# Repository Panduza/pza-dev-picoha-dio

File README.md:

# Pico Host Adapter Dio

This project aims to turn the Raspberry Pi Pico into an USB Host Adapter to control each Digital Input/Output.

## Install firmware on your Pico

[SEE Firmware Documentation](firmware/README.md)

## USB Commands

Commands on USB are based on:

- SLIP [Serial Line Internet Protocol](https://fr.wikipedia.org/wiki/Serial_Line_Internet_Protocol)
- Protobuf [From Google](https://protobuf.dev/)

The USB class used is CDC, it means that you can open it as a serial port.

You must then prepare a Protobuf message with the given specification:

```
firmware\src\api_dio.proto
```

Finally encode the message with SLIP then send it on the serial port.

## Commands examples

For example to set the pin 2 to OUTPUT (by default pins are in INPUT)

```protobuf
message PicohaDioRequest {
    RequestType type = 1;  => SET_PIN_DIRECTION OUTPUT
    uint32 pin_num = 2;    2
    PinValue value = 3;    => OUTPUT
}
```

The board should respond with

```protobuf
message PicohaDioAnswer {
    AnswerType type = 1;                => SUCCESS
    optional PinValue value = 2;
    optional string error_message = 3;
}
```

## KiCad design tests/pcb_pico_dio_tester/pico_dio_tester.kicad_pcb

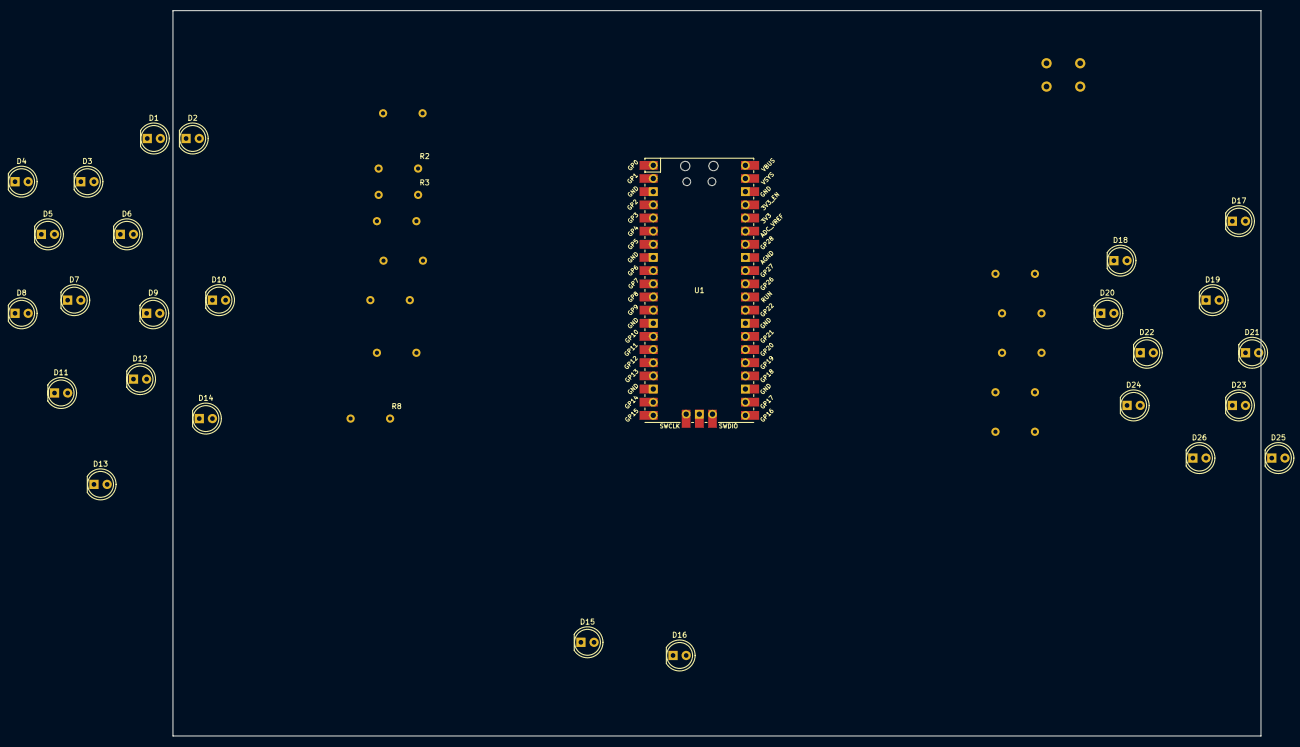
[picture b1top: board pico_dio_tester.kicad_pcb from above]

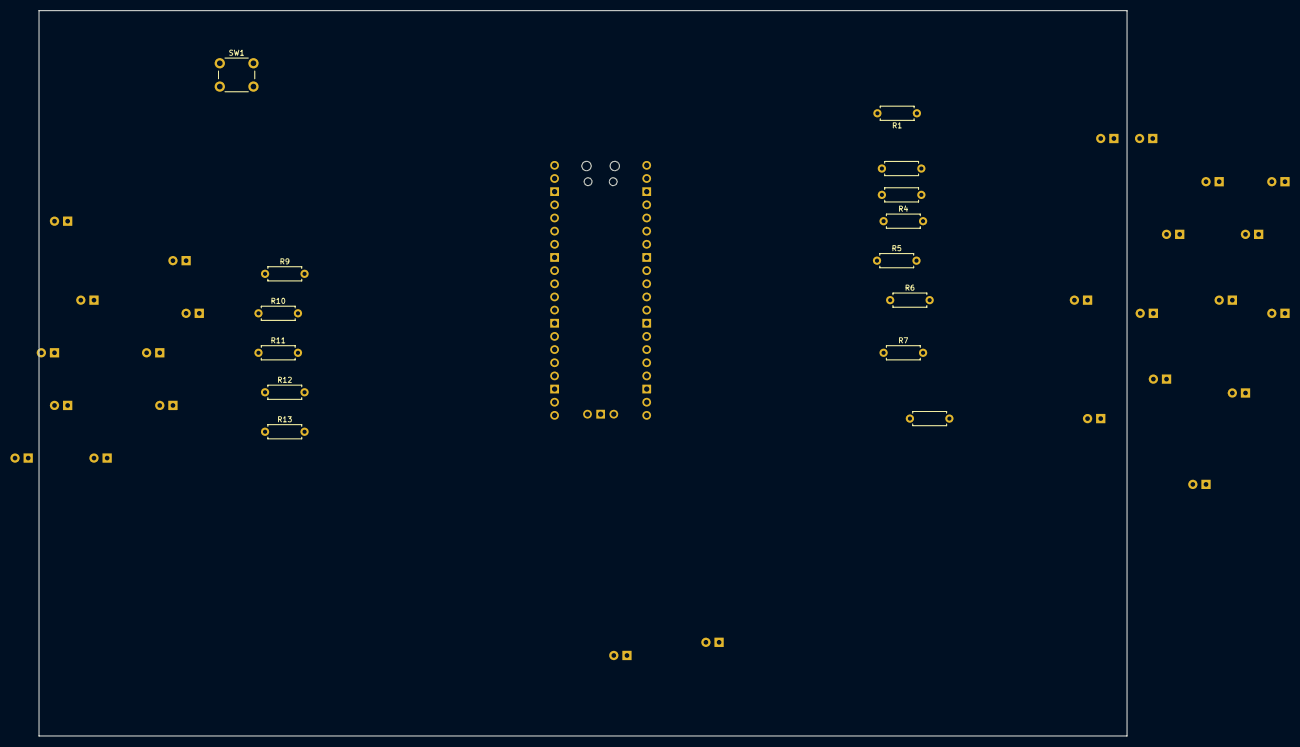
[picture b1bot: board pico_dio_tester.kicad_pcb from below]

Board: 2 copper layers, 210.0 x 140.0 mm, 41 parts (14 on the bottom side), 41 nets, no tracks yet.

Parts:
D1, D2, D3, D4, D5, D6, D7, D8, D9, D10, D11, D12, D13, D14, D15, D16, D17, D18, D19, D20, D21, D22, D23, D24, D25, D26: LD271; LED_D5.0mm_IRGrey
R1, R2, R3, R4, R5, R6, R7, R8, R9, R10, R11, R12, R13: 100R; R_Axial_DIN0207_L6.3mm_D2.5mm_P7.62mm_Horizontal
SW1: SW_Push; SW_PUSH_6mm_H5mm
U1: Pico; RPi_Pico_SMD_TH

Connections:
GND: SW1.2, U1.3 (GND), U1.8 (GND), U1.13 (GND), U1.18 (GND), U1.23 (GND), U1.28 (GND), U1.38 (GND)
GPIO_A_0: R1.2, U1.1 (GPIO0)
GPIO_A_1: R2.2, U1.4 (GPIO2)
GPIO_A_2: R3.2, U1.6 (GPIO4)
GPIO_A_3: R4.2, U1.9 (GPIO6)
GPIO_A_4: R5.2, U1.11 (GPIO8)
GPIO_A_5: R6.2, U1.14 (GPIO10)
GPIO_A_6: R7.2, U1.16 (GPIO12)
GPIO_A_7: R8.2, U1.19 (GPIO14)
GPIO_A_8: R9.2, U1.34 (GPIO28_ADC2)
GPIO_A_9: R10.2, U1.31 (GPIO26_ADC0)
GPIO_A_10: R11.2, U1.27 (GPIO21)
GPIO_A_11: R12.2, U1.25 (GPIO19)
GPIO_A_12: R13.2, U1.22 (GPIO17)
GPIO_B_0: D1.1 (K), D2.2 (A), U1.2 (GPIO1)
GPIO_B_1: D3.1 (K), D4.2 (A), U1.5 (GPIO3)
GPIO_B_2: D5.1 (K), D6.2 (A), U1.7 (GPIO5)
GPIO_B_3: D7.1 (K), D8.2 (A), U1.10 (GPIO7)
GPIO_B_4: D9.1 (K), D10.2 (A), U1.12 (GPIO9)
GPIO_B_5: D11.1 (K), D12.2 (A), U1.15 (GPIO11)
GPIO_B_6: D13.1 (K), D14.2 (A), U1.17 (GPIO13)
GPIO_B_7: D15.1 (K), D16.2 (A), U1.20 (GPIO15)
GPIO_B_8: D17.1 (K), D18.2 (A), U1.32 (GPIO27_ADC1)
GPIO_B_9: D19.1 (K), D20.2 (A), U1.29 (GPIO22)
GPIO_B_10: D21.1 (K), D22.2 (A), U1.26 (GPIO20)
GPIO_B_11: D23.1 (K), D24.2 (A), U1.24 (GPIO18)
GPIO_B_12: D25.1 (K), D26.2 (A), U1.21 (GPIO16)
unnamed: D1.2 (A), D2.1 (K), R1.1
unnamed: D3.2 (A), D4.1 (K), R2.1
unnamed: D5.2 (A), D6.1 (K), R3.1
unnamed: D7.2 (A), D8.1 (K), R4.1
unnamed: D9.2 (A), D10.1 (K), R5.1
unnamed: D11.2 (A), D12.1 (K), R6.1
unnamed: D13.2 (A), D14.1 (K), R7.1
unnamed: D15.2 (A), D16.1 (K), R8.1
unnamed: D17.2 (A), D18.1 (K), R9.1
unnamed: D19.2 (A), D20.1 (K), R10.1
unnamed: D21.2 (A), D22.1 (K), R11.1
unnamed: D23.2 (A), D24.1 (K), R12.1
unnamed: D25.2 (A), D26.1 (K), R13.1
RUN: SW1.1, U1.30 (RUN)

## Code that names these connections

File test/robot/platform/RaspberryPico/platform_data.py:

"""
This file describe Raspberry Pico test bench setup.
"""

import logging, os
from configparser import ConfigParser


_init_file = os.path.join(os.path.dirname(__file__), "config_file.ini")
PORT_COM_DUT: str = ""
if os.path.exists(_init_file):
    logging.info(f"Load config from :{_init_file}")
    _config = ConfigParser()
    _config.read(_init_file)
    PORT_COM_DUT = (
        _config.get("General", "PortCOM")
        if _config.has_option("General", "PortCOM")
        else ""
    )
else:
    logging.info(f"we didn't found: {_init_file}.")

BUILTIN_LED = 25
GPIO_UART = [0, 1]
GPIO_USABLE = [
    2,
    3,
    4,
    5,
    6,
    7,
    8,
    9,
    10,
    11,
    12,
    13,
    14,
    15,
    16,
    17,
    18,
    19,
    20,
    21,
    22,
    26,
    27,
    28,
]


def get_comp_gpio(gpio: int):
    """
       Get paired GPIO

       # Raspberry Pico test bench Setup
       To simplified the validation process GPIO are connected in pair.
               ┌──────┐--┌──────┐
     ── GPIO0  | 1    └──┘   40 |  VBUS
     ── GPIO1  | 2    USB    39 |  VSYS
          GND  | 3           38 |  GND
    ┌─  GPIO2  | 4           37 |  3V3_EN
    └─  GPIO3  | 5  [GPIO25] 36 |  3V3
    ┌─  GPIO4  | 6           35 |
    └─  GPIO5  | 7           34 |  GPIO28  ─┐
          GND  | 8   ┌    ┐  33 |  GND      |
    ┌─  GPIO6  | 9    PICO   32 |  GPIO27  ─┘
    └─  GPIO7  | 10  └    ┘  31 |  GPIO26  ─┐
    ┌─  GPIO8  | 11          30 |  Run      |
    └─  GPIO9  | 12          29 |  GPIO22  ─┘
          GND  | 13          28 |  GND
    ┌─ GPIO10  | 14          27 |  GPIO21  ─┐
    └─ GPIO11  | 15          26 |  GPIO20  ─┘
    ┌─ GPIO12  | 16          25 |  GPIO19  ─┐
    └─ GPIO13  | 17          24 |  GPIO18  ─┘
          GND  | 18          23 |  GND
    ┌─ GPIO14  | 19          22 |  GPIO17  ─┐
    └─ GPIO15  | 20   DEBUG  21 |  GPIO16  ─┘
               └───────┴┴┴──────┘

    """
    if gpio == BUILTIN_LED:
        raise ValueError("GPIO 25 is builtin LED: there is no paired GPIO to it.")
    elif gpio in GPIO_UART:
        raise ValueError("GPIO_UART are not usable: reserved for debugging propose")
    elif gpio not in GPIO_USABLE:
        raise ValueError("This gpio is not usable on this Setup.")

    elif gpio == 22:
        return 26
    elif gpio == 26:
        return 22

    elif gpio == 27:
        return 28
    elif gpio == 28:
        return 27

    else:
        return gpio - 1 if gpio % 2 else gpio + 1


# ================== Main ======================
if __name__ == "__main__":
    help(__name__)

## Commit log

2024-07-03 just import simple usb program
2024-07-05 work with no poto
2024-07-06 try femtopb
2024-07-06 femtopb seems to work
2024-07-06 move on with protobuf
2024-07-07 p with api-dio
2024-07-21 move on structure
2024-07-21 setup process callbacks
2024-07-22 found a way to do what I want
2024-07-22 restructure the code
2024-07-22 up protocole
2024-07-24 append a version of the test pcb
2024-07-24 append project robot template
2024-07-24 setup tests system
2024-07-24 start test impl
2024-07-25 change dir organization to inlcude cucumber tests
2024-07-25 setup tests ping
2024-07-25 update ping test
2024-07-26 ping test ok
2024-07-26 use the new buffer stream slip
2024-07-26 more tests
2024-07-28 minor update
2024-08-09 Append a minimal set of documentation
2024-09-05 Creat Robot test from Template
2024-09-09 Use SLIP and PROTOBUF
2024-09-10 Update gpio keysworlds
2024-09-10 Update keyworlds
2024-09-11 Small fix and update
2024-09-12 init pin as input
2024-09-12 move on
2024-09-13 Revome file how should not be commited
2024-09-13 need to manage get value
2024-09-13 fix get value
2024-09-16 Fix list in Robot
2024-09-16 Small update+fix and documentation
2024-09-20 Renaming Var
2024-09-20 Update link with Keyworlds
2024-09-20 Fix 'output error must be FAILURE'
2024-09-20 Handle Timout + renaming Var
2024-09-26 line to generate the elf
2024-10-11 Update error output + Update connection to serial COM
2024-10-11 Update platform ressource + Doc
2024-10-11 Update keyword name
2024-10-11 Update Readme + requirement
2024-10-11 Just Python formating with Black Formatter extention
2024-10-11 Update 'logging' output
2024-10-18 Add uf2 file in gitignore
2024-10-18 Update Ping and add documentation
2024-11-25 Fix operations (#6)
2024-11-25 Robot framework test dev (#5)
    * Creat Robot test from Template
    * Use SLIP and PROTOBUF
    * Update gpio keysworlds
    * Update keyworlds
    * Small fix and update
    * Update readme
2024-11-25 improve picoha serial number identification
2024-11-25 change the serial number, no _ should be present in it
2024-12-13 update rustc support
2024-12-29 minor updates
2024-12-30 style refactoring
2024-12-30 change input reading
2024-12-30 fix some wanring
2024-12-30 Fix direction management (#7)
    * style refactoring
    * change input reading
    * fix some wanring
    * fix direction management
2024-12-30 fix direction management
2025-01-08 Fix Impossible to use pin 26, 27 #3
2025-01-14 WA the system does not crask when using an not existing pin
2025-01-14 Update Log Level to TRACE + small test fix
2025-01-14 Update Documentation
2025-01-17 Create Python Non-regretion Test suite
2025-01-17 Fix test
2025-01-20 Update Doc on Python Non-Reg test suite
2025-01-21 Add error message when gpio is not available
2025-01-21 Update pyhton test API
2025-01-21 Update Test of non regression
2025-01-21 Fix wrong indentation
2025-01-21 fix keyword 'output error must be FAILURE'
2025-01-22 Retrieve ticket name from first line description
2025-01-22 revert last commit
2025-01-22 Amend
2025-01-24 Fix requirements: sliplib V0.7.0 not work on this project
2025-01-28 Use Pytest for python test
2025-01-28 Return from code review : - Fix MAX_PINS const is duplicated - Add Return type in API - Use port com as parameter in test - Fix tipos
2025-01-28 return from Code Review: - fix typo - factorization
2025-01-29 Move config file
2025-01-29 Add extension recommendation file
2025-01-29 Fix warnings
2025-01-29 Format code with
2025-01-30 Remove static mut UART_DEBUG
2025-01-30 Rework main.rs
2025-01-31 Rework dio_request_processor.rs
2025-01-31 Add fix to use GPIO pins 26,27,28
2025-02-03 Fix typo
2025-02-03 Add output msg on assert
2025-02-17 Remove some warnings in tests
2025-02-17 Fix USB regression : invalid serial not supported by Windows
2025-02-19 Update Python
2025-02-19 Update Robot + Add Test USB COM
2025-02-19 Add Workspace File
2025-02-19 Fix warn
2025-02-20 Migrate to embassy framework
2025-02-20 Small Cleaning
2025-02-21 Add benchmark test
2025-02-24 Remove some warnings
2025-02-24 Little simplifications
2025-02-26 Replace UART logger by an additional USB Serial line available when compiling in DEBUG mode (remove features=uart0_debug)
2025-03-04 Improve test coverage
2025-03-04 Minor fix
2025-03-04 Split PROTO PinValue enum into PinValue and PinDirection
2025-03-04 Write custom decoding/encoding (SLIP + femtopb) functions to speed up processing
2025-03-11 Update test: - Remove keywords.py - Update USB test
2025-03-14 Update README.md : fix tipo
2025-03-19 Create draft for nginx server
2025-03-19 Add docker file
2025-03-24 Remove 'Call Methode' from robot
2025-03-24 Update doc
2025-03-25 Update docker & www
2025-03-25 Clean & update
2025-03-27 Small update + Doc
2025-03-27 Update www
2025-03-31 Clean & doc
2025-03-31 Fix tests
2026-05-28 base of the project blink
2026-05-29 append gitignore
2026-05-29 ok move west manifest
2026-05-29 test mini manifest
2026-05-29 just the dep pico
2026-05-29 take only hal pico
2026-05-29 init script
2026-05-30 blink build ok
2026-05-30 extend gitingnore
